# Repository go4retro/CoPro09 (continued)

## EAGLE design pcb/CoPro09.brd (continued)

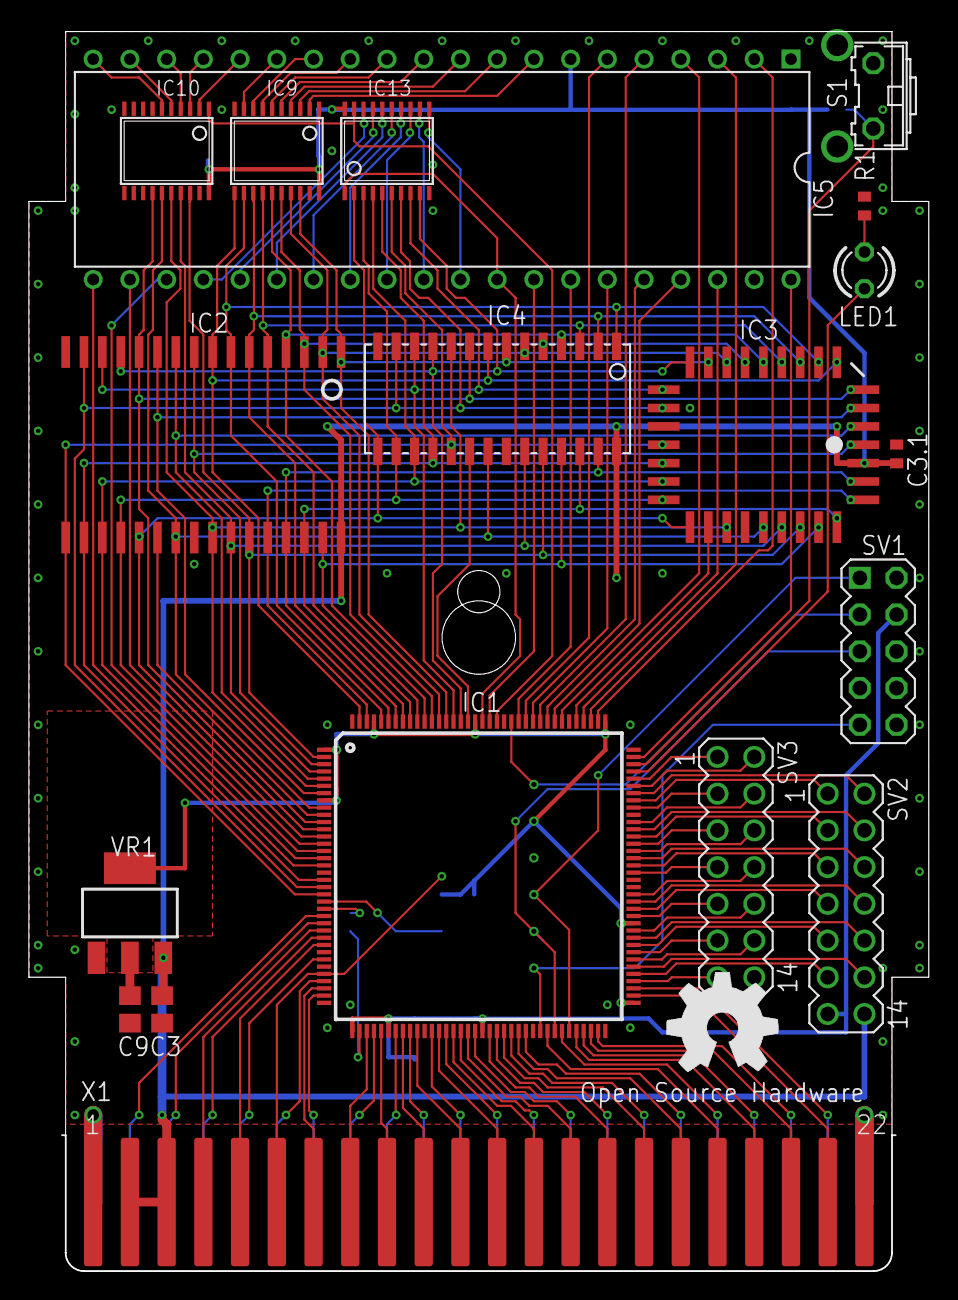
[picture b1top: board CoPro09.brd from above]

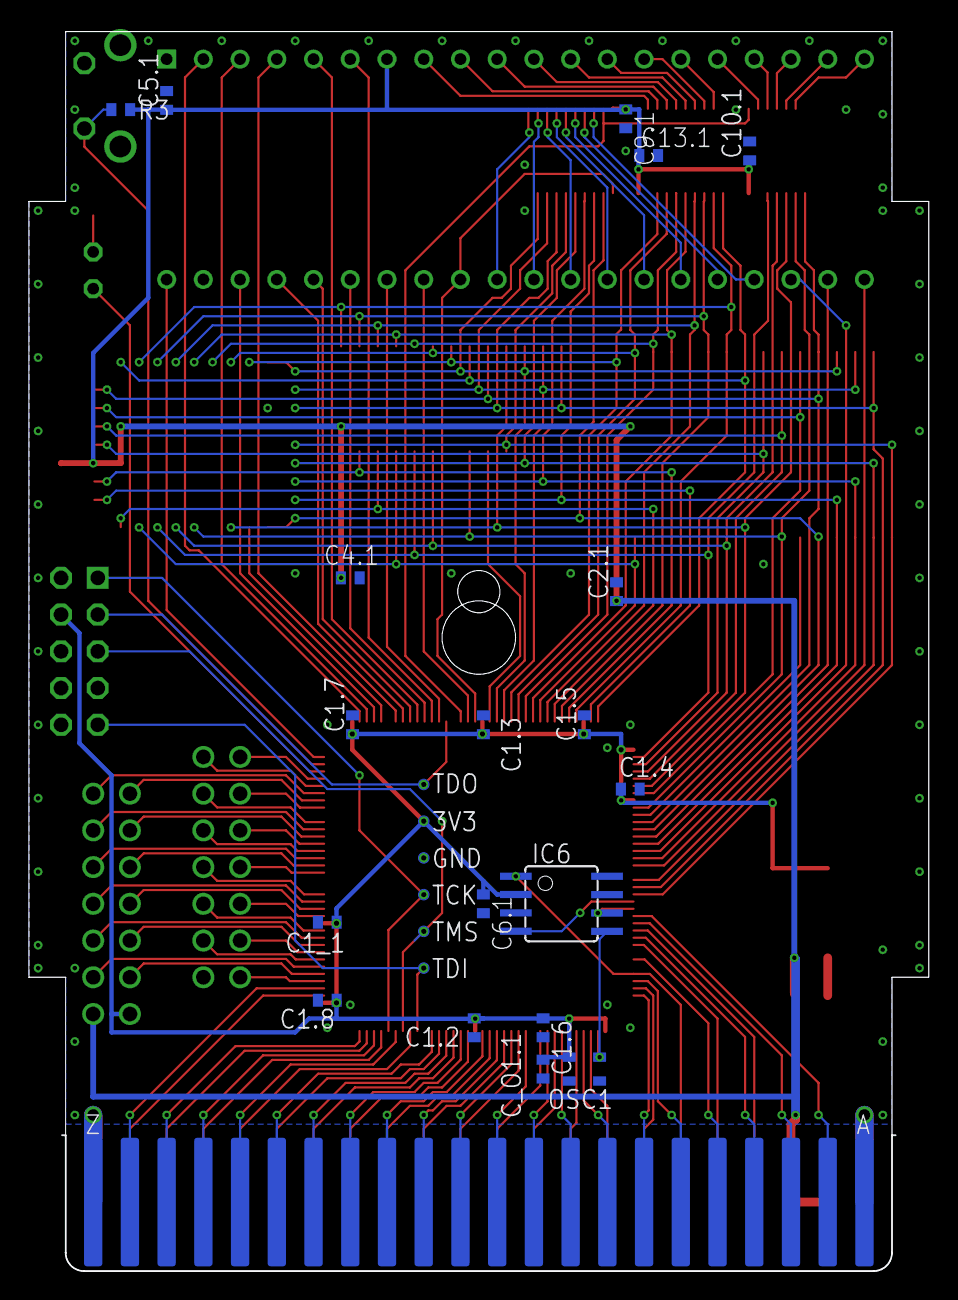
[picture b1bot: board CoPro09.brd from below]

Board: 2 copper layers, 62.2 x 85.7 mm, 46 parts (25 on the bottom side), 145 nets.

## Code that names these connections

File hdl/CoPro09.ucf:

#PACE: Start of Constraints generated by PACE

#PACE: Start of PACE I/O Pin Assignments
NET "_ce_dat"  LOC = "P128"  ; 
NET "_ce_ram"  LOC = "P10"  ; 
NET "_enbus"  LOC = "P124"  ; 
NET "_exrom"  LOC = "P41"  ; 
NET "_firq_09"  LOC = "P115"  ;
NET "_game"  LOC = "P39"  ; 
NET "_halt_09"  LOC = "P107"  ; 
NET "_io<1>"  LOC = "P34"  ; 
NET "_io<2>"  LOC = "P44"  ; 
NET "_irq_09"  LOC = "P111"  ;
NET "_nmi_09"  LOC = "P110"  ;
NET "_reset"  LOC = "P25"  ; 
NET "_reset_09"  LOC = "P116"  ; 
NET "_we_mem"  LOC = "P139"  ; 
NET "address_09<13>"  LOC = "P17"  ; 
NET "address_09<14>"  LOC = "P13"  ; 
NET "address_09<15>"  LOC = "P15"  ; 
NET "address_cpu<0>"  LOC = "P75"  ; 
NET "address_cpu<10>"  LOC = "P48"  ; 
NET "address_cpu<11>"  LOC = "P45"  ; 
NET "address_cpu<12>"  LOC = "P43"  ; 
NET "address_cpu<13>"  LOC = "P40"  ; 
NET "address_cpu<14>"  LOC = "P35"  ; 
NET "address_cpu<15>"  LOC = "P33"  ; 
NET "address_cpu<1>"  LOC = "P71"  ; 
NET "address_cpu<2>"  LOC = "P69"  ; 
NET "address_cpu<3>"  LOC = "P66"  ; 
NET "address_cpu<4>"  LOC = "P61"  ; 
NET "address_cpu<5>"  LOC = "P59"  ; 
NET "address_cpu<6>"  LOC = "P57"  ; 
NET "address_cpu<7>"  LOC = "P54"  ; 
NET "address_cpu<8>"  LOC = "P52"  ; 
NET "address_cpu<9>"  LOC = "P50"  ; 
NET "address_mem<0>"  LOC = "P131"  ; 
NET "address_mem<10>"  LOC = "P6"  ; 
NET "address_mem<11>"  LOC = "P9"  ; 
NET "address_mem<12>"  LOC = "P11"  ; 
NET "address_mem<13>"  LOC = "P135"  ; 
NET "address_mem<14>"  LOC = "P137"  ; 
NET "address_mem<15>"  LOC = "P7"  ; 
NET "address_mem<16>"  LOC = "P5"  ; 
NET "address_mem<17>"  LOC = "P142"  ; 
NET "address_mem<18>"  LOC = "P3"  ; 
NET "address_mem<1>"  LOC = "P132"  ; 
NET "address_mem<2>"  LOC = "P133"  ; 
NET "address_mem<3>"  LOC = "P134"  ; 
NET "address_mem<4>"  LOC = "P136"  ; 
NET "address_mem<5>"  LOC = "P138"  ; 
NET "address_mem<6>"  LOC = "P140"  ; 
NET "address_mem<7>"  LOC = "P143"  ; 
NET "address_mem<8>"  LOC = "P2"  ; 
NET "address_mem<9>"  LOC = "P4"  ; 
NET "clk_cfg<0>"  LOC = "P23"  ; 
NET "clk_cfg<1>"  LOC = "P22"  ; 
NET "clk_mult"  LOC = "P38"  ; 
NET "clock"  LOC = "P30"  ; 
NET "clock_e"  LOC = "P121"  ; 
NET "clock_q"  LOC = "P119"  ; 
NET "data_cpu<0>"  LOC = "P74"  ; 
NET "data_cpu<1>"  LOC = "P70"  ; 
NET "data_cpu<2>"  LOC = "P68"  ; 
NET "data_cpu<3>"  LOC = "P64"  ; 
NET "data_cpu<4>"  LOC = "P60"  ; 
NET "data_cpu<5>"  LOC = "P58"  ; 
NET "data_cpu<6>"  LOC = "P56"  ; 
NET "data_cpu<7>"  LOC = "P53"  ; 
NET "data_mem<0>"  LOC = "P129"  ; 
NET "data_mem<1>"  LOC = "P130"  ; 
NET "data_mem<2>"  LOC = "P20"  ; 
NET "data_mem<3>"  LOC = "P21"  ; 
NET "data_mem<4>"  LOC = "P19"  ; 
NET "data_mem<5>"  LOC = "P16"  ; 
NET "data_mem<6>"  LOC = "P14"  ; 
NET "data_mem<7>"  LOC = "P12"  ; 
NET "dotclk"  LOC = "P32"  ; 
NET "led"  LOC = "P105"  ; 
NET "r_w"  LOC = "P28"  ; 
NET "r_w_09"  LOC = "P126"  ; 
NET "test<0>"  LOC = "P101"  ; 
NET "test<1>"  LOC = "P102"  ; 
NET "test<2>"  LOC = "P96"  ; 
NET "test<3>"  LOC = "P97"  ; 
NET "test<4>"  LOC = "P92"  ; 
NET "test<5>"  LOC = "P93"  ; 
NET "test<6>"  LOC = "P86"  ; 
NET "test<7>"  LOC = "P87"  ; 

#PACE: Start of PACE Area Constraints

#PACE: Start of PACE Prohibit Constraints

#PACE: End of Constraints generated by PACE

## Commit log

2018-05-25 Created shared memory space in IO1 and enabled 63c09e operation
2018-06-09 configurable working 1MHz/working 4MHz/partially working 5MHz compilation
